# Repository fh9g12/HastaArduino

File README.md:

# HastaArduino

Bench- and wind-tunnel instrumentation for a free-to-pitch / control-surface aircraft model: firmware for a Pimoroni Pico Plus 2 (WiFi via an RM2 breakout) and the MATLAB package (`wt.hasta`) that drives it over SCPI/TCP.

**Documentation: [docs/README.md](docs/README.md)** covers the architecture, wire protocol, MATLAB package, coding conventions, testing approach, safety rules for anyone (human or agent) changing or running it, and the known gotchas and open items.

Quick orientation:

* `HastaDAQ/` is the flagship firmware; `HastaDrivers/` the shared driver library.
* `matlab/hastadaq/` is the MATLAB side (`+wt/+hasta`, `+wt/+runNum`, `+scripts`).
* `kicad/` and `wiring/` hold the schematic and cable diagrams.

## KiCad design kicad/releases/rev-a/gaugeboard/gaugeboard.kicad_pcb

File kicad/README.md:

# kicad/: schematics, PCB layout and fabrication

Everything electrical for the HastaDAQ REV A hardware. Two boards: the **main board** (`hastadaq/`) and the
**strain-gauge board** (`gaugeboard/`), joined by a 4-wire I2C loom (GND, +5V, SDA, SCL). Design decisions and
the per-board briefs are in `../docs/` (`PCB_BRIEF.md`, `PCB_BRIEF_GAUGE.md`, `PARTS_TO_SELECT.md`); the repo-wide
overview is `../docs/README.md`. This file covers the *workflow*, the *tools* and what a new agent or person
needs to know before laying out the next board.

## Status (2026-10-27)

| Board | Schematic | PCB layout | Fabrication |
|---|---|---|---|
| Gauge board (`gaugeboard/`) | done, ERC clean | **done**, DRC clean (only cosmetic library-mismatch warnings) | **ordered from PCBWay 2026-10-27** (board type, single or panel, chosen by the owner) |
| Main board (`hastadaq/`) | done, ERC clean; **changed 2026-10-27**: ENC4 removed, two RM08 SSI headers added | **done**: placed, routed, DRC clean (`releases/rev-a/hastadaq/hastadaq.kicad_pcb`) | **ordered from PCBWay 2026-10-28** |

**Both boards are in ONE final revision folder, `releases/rev-a/`** (merged 2026-10-28 from the earlier `20261026-2252-rev-a` and
`rev-a` releases, which are gone from the tree; git history has them):

* `releases/rev-a/gaugeboard/`: the gauge board as ordered (2026-10-27), with `gaugeboard.kicad_pcb` and the exact fab files in `fab/`
  (`gaugeboard_gerbers.zip` and `gerbers/`). Its `fp-lib-table` reads the shared footprints from `../hastadaq/HastaDAQ.pretty`.
* `releases/rev-a/hastadaq/`: the main board as ordered (2026-10-28; the schematic has the three SPI encoder ports ENC1-ENC3 and the
  two RM08 SSI headers J6/J11, see `../docs/PCB_BRIEF.md`), with `hastadaq.kicad_pcb` and its fab files in `fab/`.
* `releases/rev-a/docs/`, `wiring/`, `START_HERE.md`, `PUBLISHED.md`: the briefs and loom diagram from the later snapshot.
  `UoBLogo.kicad_mod` is the logo footprint from the gauge-board release.

**Commit this folder**: it is the as-built record. The gauge board's schematic was identical in both snapshots (only the netlist
timestamp differed), so nothing in the ordered gauge board changed in the merge. For a respin, `publish.py` into a NEW folder.

Not verified on hardware yet: the second ADS122C04's address (expected 0x41), I2C over the loom, servo noise
on the gauge board's 3V3. The Gerbers were checked by DRC and by counting holes against the board, not in a
third-party Gerber viewer (the owner looked at PCBWay's preview).

## Folder map

```
hastadaq/                 main board: schematic, symbol library, HastaDAQ.pretty (footprints shared by BOTH boards)
gaugeboard/               gauge board: schematic (working copy; the PCB is in a release folder, see below)
releases/<stamp>-rev-a/   frozen snapshot made by publish.py: schematics, netlists, docs and (once started) the .kicad_pcb
                          files and fab/ output. LAY OUT AND ORDER FROM A RELEASE FOLDER, never from hastadaq/ or gaugeboard/.
tools/                    generators and helpers (see below)
tools/layout/             layout, routing, silkscreen and fab scripts (see tools/layout/README.md)
```

## Workflow

1. **Schematic** (bootstrap only): `py kicad/tools/generate_gauge_sch.py` / `generate_hastadaq_sch.py`. These reassign
   reference designators and UUIDs on every run, so they are only for the time **before** a `.kicad_pcb` exists.
2. **Publish**: `py kicad/tools/publish.py --label rev-a` copies both schematics, libraries, netlists, PDFs and the docs
   into a new `releases/<date-time>-rev-a/` folder (it refuses to run if ERC is not clean). Releases are never overwritten.
3. **Lay out inside the release folder**: open `<board>.kicad_pro`, create `<board>.kicad_pcb`, Tools > Update PCB from
   Schematic. From here on **edit the schematic in KiCad and never re-run a generator over that release**. If the schematic
   needs a big change, delete or abandon the release, fix the generator, and publish a NEW one (this happened once: J3/J4
   became 2x3 headers, the first release was deleted and `20261026-2252-rev-a` replaced it; that one and `20261027-2346-rev-a-ssi` were later merged into `releases/rev-a`).
4. **Fab files**: `py kicad/tools/layout/export_fab.py releases/<rel>/<board>/<board>.kicad_pcb`
   (Gerbers + drill + zip, the PCBWay upload). Close the PCB editor first.
5. Check before ordering: `kicad-cli pcb drc --refill-zones --schematic-parity ...` shows no errors and "0 unconnected pads".

## Tools on this machine

* KiCad 10.0.6 is installed per user at `%LOCALAPPDATA%\Programs\KiCad\10.0\bin\` (not on PATH): `kicad-cli.exe` (ERC, DRC,
  netlist, Gerbers, SVG/3D render) and `python.exe` with the `pcbnew` API. Use that `python.exe` for any script that
  touches a board (the system `py` has no pcbnew).
* **No autorouter ships with KiCad.** The gauge board was routed by script (`tools/layout/gauge_route_as_built.py`).
  See "Faster routing for future boards" below.
* Previews: `kicad-cli pcb render` crops oddly; for a whole-board picture use `kicad-cli pcb export svg` (layers
  `F.Cu,B.Cu,F.SilkS,Edge.Cuts`, `--mode-single --page-size-mode 2`) and rasterise with `pymupdf`.
* `kicad-cli pcb drc --refill-zones` refills zones first; without it the report can use stale pour fills.

## Rules of the road (learned on the gauge board)

* **Check for the PCB editor before writing a board file.** A `~<name>.kicad_pcb.lck` next to the file means it is open.
  Also compare a hash of the file with your last write: the owner edits the layout by hand between your steps (they moved
  parts, resized the board, added a logo). Back the file up first. Never silently overwrite their placement.
* The owner wants **placement reviewed first, routing only after an explicit go**.
* They notice cosmetic problems: messy or ambiguous silkscreen labels, and "unnecessary" vias (stitching vias under a
  module). Look at a render of both sides before calling a layout done.
* pcbnew API notes: `pads = fp.Pads()` then iterate it (do not wrap it in `list()`); `fp.Remove(pad)` works;
  net names from the netlist start with `/` (`/+3V3`, `/SDA`); a footprint's `path` is the schematic symbol UUID, which is
  what keeps "Update PCB from Schematic" from duplicating parts. Do not name a script `inspect.py` (it shadows the stdlib).
* The ADS122C04 library footprint still carries four 2.5 mm mounting holes. On the gauge board they were removed from the
  BOARD only (`tools/layout/remove_pads.py`); "Update footprints from library" would restore them.
* **Check that every part got its nets** after building a board from a netlist: `python.exe tools/layout/check_pad_nets.py <pcb> <net>`.
  A symbol whose pin numbers differ from its footprint's pad numbers gets no nets (no ratsnest). This hit D1-D4 on the main board
  (symbol pins A/K vs KiCad diode footprints pads 1 = cathode / 2 = anode); the generators now number diode pins 1 (K) and 2 (A).
* On the main board the parts hidden under the Pico make KiCad report `pth_inside_courtyard`; the project ignores that rule (`tools/layout/set_pcbway_rules.py --ignore pth_inside_courtyard`). Run that script LAST: something in a longer command sequence reset it once.
* `lib_footprint_mismatch` DRC warnings ("local override") are cosmetic: text moved or fields edited on a footprint.
* `kicad-cli pcb export gerbers` writes a date into every file header, so re-exports differ byte-for-byte but not in content.

## Fabrication settings used (PCBWay, 2 layers)

1.6 mm FR4, 1 oz copper, min track/space 6/6 mil (0.1524 mm), min drill 0.3 mm, copper-to-edge 0.3 mm. Default net class:
0.25 mm track, 0.2 mm clearance, 0.6/0.3 mm via (`tools/layout/set_pcbway_rules.py` writes these into the `.kicad_pro`).
Stay inside 100 x 100 mm (PCBWay's cheapest quote tier). Everything on the top face, all connectors vertical 0.1 in
headers, M3 holes (3.2 mm) 4 mm in from each corner, copper pour kept 3.25 mm (radius) from each hole for the screw head.
Reference text 0.8 mm, horizontal. PCBWay's own help for the board-type options (single / panel by customer / panel by
PCBWay) is at pcbway.com/helpcenter/ordering_parameter_instruction/Board_type.html.

## Gauge board as built (rev A)

* 54.22 x 49.60 mm, 3 mm corner radius, M3 holes 46 x 41.5 mm apart. Layout (owner's final, hand-adjusted): loom J1/J2 as
  horizontal rows at the top left; C1, C2, U1 (LDO), C3, C4 and the test points down the left; R5/R6 (completion pair)
  vertical at the lower left; ADS122C04 breakouts U2 above U3, both rotated 180 degrees (digital row on top); R2/C5/R1
  between the modules and R4/C6/R3 below U3 (the optional filter positions); gauge headers J4 above J3 on the right (2x3
  each, rows V V / SIG SIG / GND GND). Logo and "STRAIN GAUGE BREAKOUT" text are on the back silkscreen.
* Routing (all scripted): horizontals on F.Cu, verticals on B.Cu; +3V3 is a trunk from the LDO to both ADCs and J3/J4;
  SDA/SCL run as a two-wire bus on the left; GND is a pour on both layers with 21 stitching vias outside the modules.
* **ADS_REF**: the two legs from the R5/R6 midpoint to R2.1 and R4.1 are equal (12.05 mm each).
* **SIG paths are not matched**: SIG1 4.7 mm, SIG2 37.2 mm, because J4 sits above J3 while R3 is at the bottom. Accepted by
  the owner (DC bridge signal); swapping J3/J4 or moving R3/C6 nearer J4 would fix it on a respin.
* Fab: 103 plated holes (0.3, 0.75, 0.8, 1.0 mm) and 4 non-plated M3 holes (3.2 mm).

## Next: the main board

* Brief: `../docs/PCB_BRIEF.md` (section 0 decisions, section 7 placement guidelines). Pico Plus 2 is 51 x 21 mm, the Pololu is
  6.1 mm tall, USB-C at the top, supply connector and Pololu at one end, loom and IMU headers at the Pico end.
* Main-board loom J2 must keep the order GND, +5V, SDA, SCL (same as gauge J1) and 3.3 V logic on SDA/SCL.
* Big supply paths: `+12V`, `VSERVO` (8.4 V, 5 A rail) and returns need wide traces or pours. Do not let the default 0.25 mm
  net class touch them.
* **Placed by the owner and first-attempt ROUTED (2026-10-28)** in `releases/rev-a/hastadaq/`: 62.1 x 89.4 mm, Pico top left, 5 V + 8.4 V supplies top right, encoders / I2C + supply cable / SBUS along the bottom, **12 small parts hidden under the Pico on the BOTTOM side** (see `../docs/PCB_BRIEF.md`) and a 20 mm plug-clearance strip behind the Pico (no COMPONENTS there; copper is allowed, `ROUTE_KEEP_TOP=1` restores the old no-top-copper rule). Routed with `tools/layout/route_main.py` (custom grid router, see `tools/layout/README.md`): VSERVO 2.0 mm bar on F.Cu down the J7 middle column, +12V 2.0 mm bar on B.Cu, +5V/+5V_VSYS 0.8 mm, +3V3 0.5 mm, signals 0.25 mm, GND pours on both layers. DRC (PCBWay 6/6 mil rules): no errors, no unconnected items; 18 `silk_over_copper` (part outlines clipped by mask, cosmetic), 1 `silk_overlap` (D4's "K" against R14), 2 `footprint_symbol_mismatch` (TP1/TP2 BOM flag), 2 `lib_footprint_mismatch` (both edited on this board only, library unchanged, so "Update footprints from library" would undo them: U2, the Pololu's three mounting holes removed with `remove_pads.py U2 --npth-only`; U1, the Pico footprint's Pico-W "Antenna Copper Keep Out" shortened by 3 mm with `trim_fp_keepout.py U1 3`, which is harmless for the Plus 2 but cuts into the antenna area if a Pico 2 W is ever fitted). The Pico mid-row GND pins 18 and 23 are bridged by a 0.5 mm B.Cu GND track across that freed strip. Fab files (7 Gerber layers + drills, zip for upload) are in `releases/rev-a/hastadaq/fab/` (made with `export_fab.py` after the owner's silkscreen edits; 4 NPTH holes, 298 PTH). Ordered from PCBWay 2026-10-28. Do NOT re-run `route_main.py` over a board whose routing the owner has edited. New this revision: the two SSI headers J6 and J11
  (3V3, GND, CLK, DATA) on GP17-GP19, which are on the Pico's lower right pins with the USB-C at the top, so place them there; the
  RLS RM08 encoders connect through inline LDB02 boards the owner fits near the Pico. The firmware for them is `HastaDrivers/src/Rm08Ssi.h`
  (PIO), not yet run on hardware.

## Faster routing for future boards

The gauge board (about 50 connections) took many iterations of hand-planned coordinates. The main board has far more
(Pico, six servo plugs, four SPI encoder ports, trigger and soft-stop circuits), so scripting every track by hand will not scale.
[KiCadRoutingTools](https://github.com/drandyhaas/KiCadRoutingTools) (MIT, Rust-accelerated A* router, KiCad 9/10, plugin and
CLI, plane pours, power-net widths, DRC and connectivity checkers) looks like a good fit **for the non-critical nets**.
This was judged from its README only; it has not been run here. Suggested trial: copy the main board, place parts by hand
first, route GND as a pour, let the tool route the logic nets, hand-route power and anything noise-critical, then run
`kicad-cli pcb drc --refill-zones` and review in KiCad. Install from KiCad's Plugin and Content Manager or build from source
rather than running an unvetted binary. Known limits per its README: no push-and-shove, no blind/buried vias; behaviour on a
2-layer through-hole board is not documented, so test before trusting.

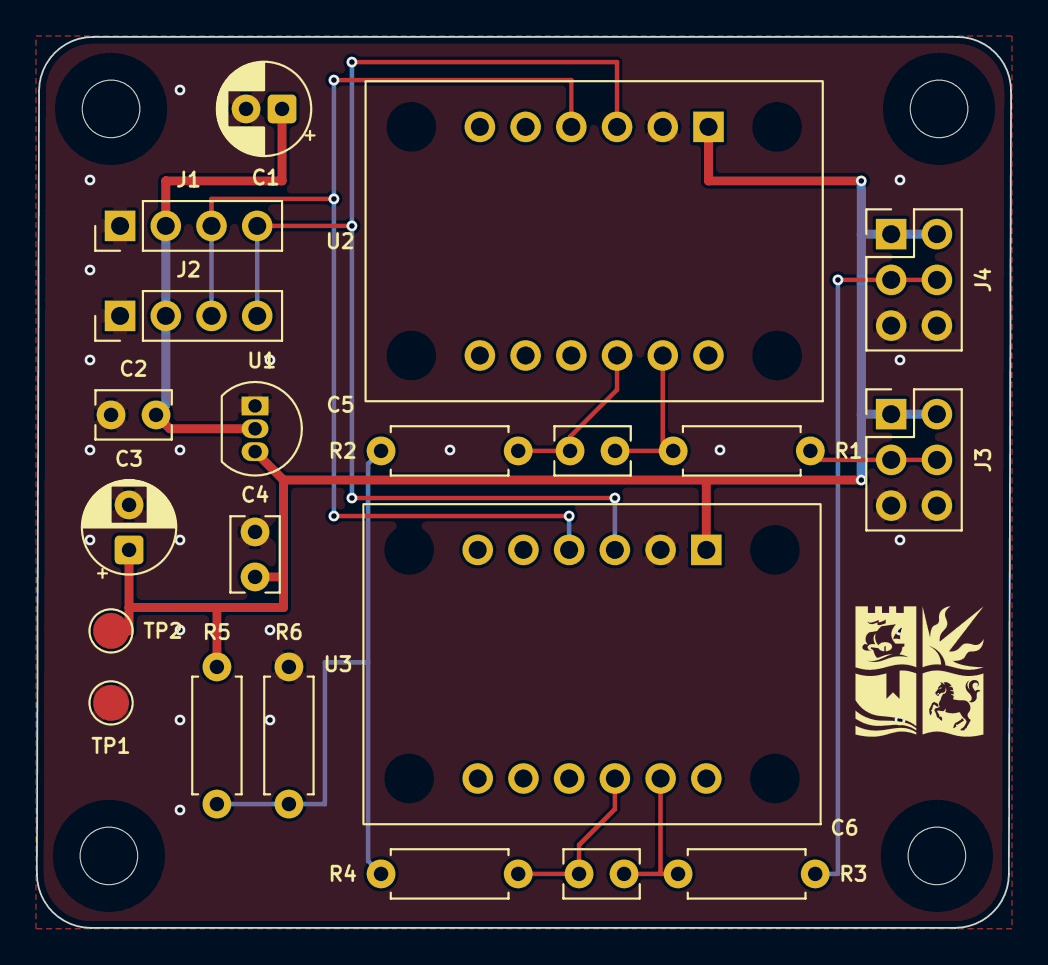
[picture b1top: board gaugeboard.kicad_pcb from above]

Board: 2 copper layers, 54.1 x 49.5 mm, 25 parts (0 on the bottom side), 12 nets.

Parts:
C1: 47uF 16V (RS PRO LHK 5x7); CP_Radial_D5.0mm_P2.00mm
C2, C4: 100nF 50V X7R (Vishay K104); C_Rect_L4.0mm_W2.5mm_P2.50mm
C3: 10uF 10V tantalum (RS PRO CB, + to 3V3); CP_Radial_D5.0mm_P2.50mm
C5, C6: 100nF 50V X7R (DNP); C_Rect_L4.0mm_W2.5mm_P2.50mm
H1, H2, H3, H4: MountingHole_3.2mm_M3
J1: LOOM from main board (4-wire I2C): GND, +5V, SDA,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; PinHeader_1x04_P2.54mm_Vertical
J2: LOOM OUT (pass-through, paralleled with J1): GND,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; PinHeader_1x04_P2.54mm_Vertical
J3: HB1 half-bridge #1 (on beam), 2x3: V V / SIG SIG 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; PinHeader_2x03_P2.54mm_Vertical
J4: HB2 half-bridge #2 (on beam), 2x3: V V / SIG SIG 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; PinHeader_2x03_P2.54mm_Vertical
R1, R2, R3, R4: 0R link; R_Axial_DIN0207_L6.3mm_D2.5mm_P7.62mm_Horizontal
R5, R6: 350R fixed; R_Axial_DIN0207_L6.3mm_D2.5mm_P7.62mm_Horizontal
TP1, TP2: TP; TestPoint_Pad_D2.0mm
U1: 3.3 V LDO: MCP1700-3302E/TO (TO-92: pin 1 GND, 2 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; TO-92_Inline
U2: Adafruit ADS122C04 #1 (I2C 0x40); Adafruit_ADS122C04_Breakout
U3: Adafruit ADS122C04 #2 (address jumper bridged); Adafruit_ADS122C04_Breakout

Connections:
/+3V3: C3.1 (+), C4.1, J3.1 (V), J3.2 (V), J4.1 (V), J4.2 (V), R5.1, TP2.1, U1.3 (VOUT), U2.1 (VIN), U3.1 (VIN)
/+5V: C1.1 (+), C2.1, J1.2 (5V), J2.2 (5V), U1.2 (VIN)
/ADS1_A0: C5.1, R1.2, U2.7 (A0)
/ADS1_A1: C5.2, R2.2, U2.8 (A1)
/ADS1_SIG: J3.3 (SIG), J3.4 (SIG), R1.1
/ADS2_A0: C6.1, R3.2, U3.7 (A0)
/ADS2_A1: C6.2, R4.2, U3.8 (A1)
/ADS2_SIG: J4.3 (SIG), J4.4 (SIG), R3.1
/ADS_REF: R2.1, R4.1, R5.2, R6.1
/GND: C1.2 (-), C2.2, C3.2 (-), C4.2, J1.1 (GND), J2.1 (GND), J3.5 (GND), J3.6 (GND), J4.5 (GND), J4.6 (GND), R6.2, TP1.1, U1.1 (GND), U2.2 (GND), U3.2 (GND)
/SCL: J1.4 (SCL), J2.4 (SCL), U2.4 (SCL), U3.4 (SCL)
/SDA: J1.3 (SDA), J2.3 (SDA), U2.3 (SDA), U3.3 (SDA)

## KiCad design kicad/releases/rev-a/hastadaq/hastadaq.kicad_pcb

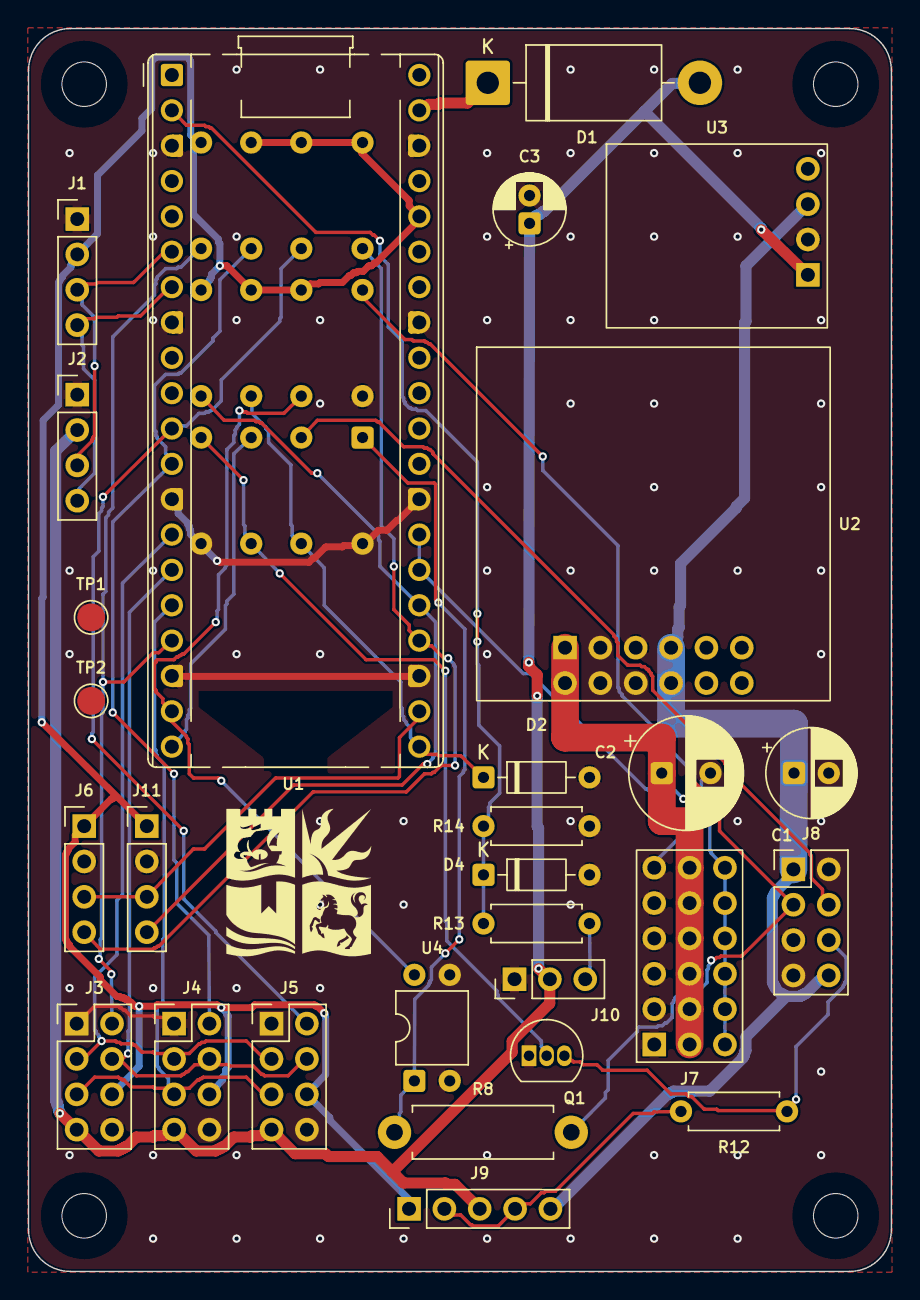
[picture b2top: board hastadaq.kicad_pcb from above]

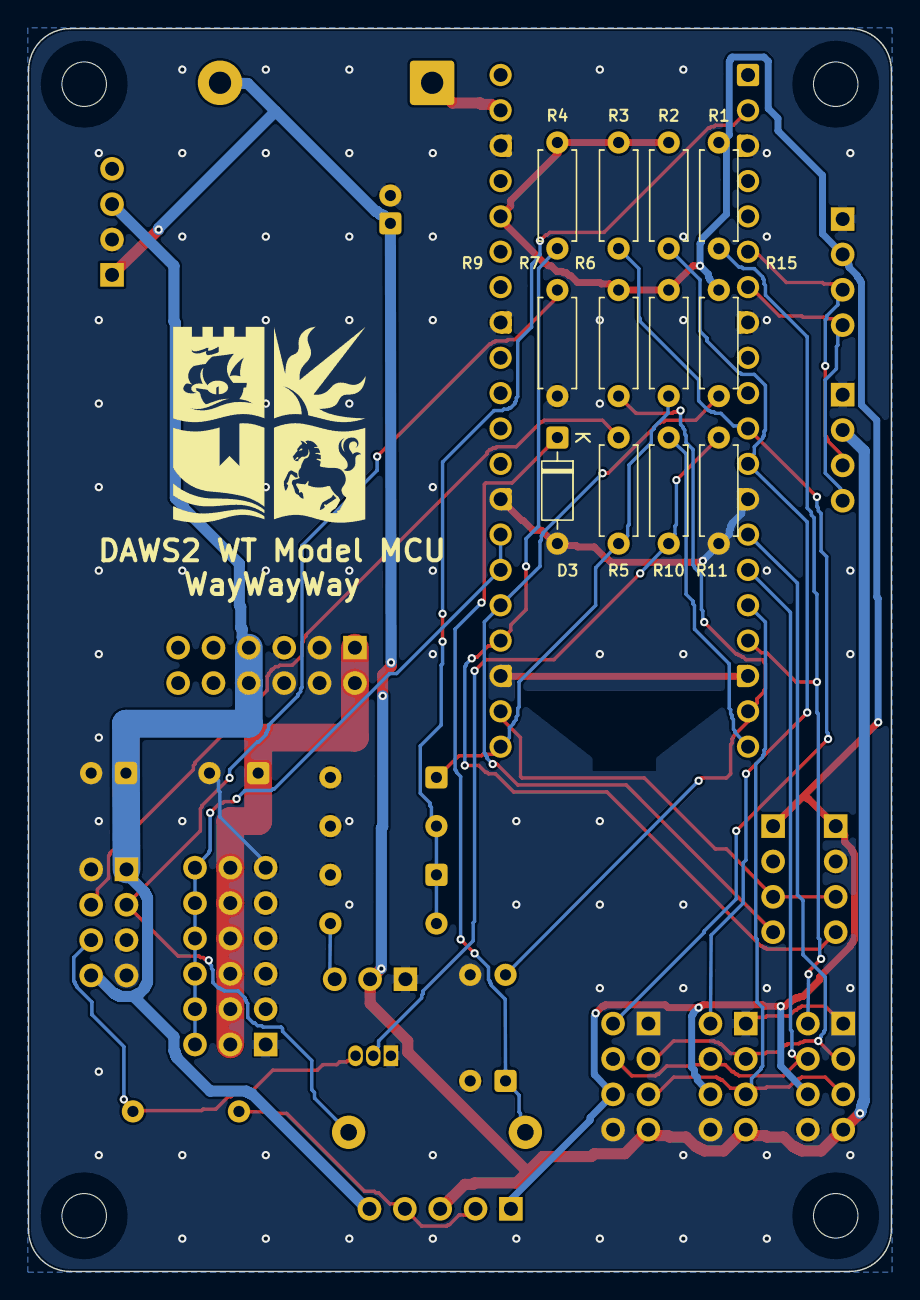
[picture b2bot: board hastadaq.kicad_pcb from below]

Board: 2 copper layers, 62.0 x 89.3 mm, 44 parts (12 on the bottom side), 29 nets.

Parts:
C1: 100uF 25V input bulk (Panasonic ECA1EM101); CP_Radial_D6.3mm_P2.50mm
C2: 470uF 16V servo bulk (Panasonic EEUFR1C471); CP_Radial_D8.0mm_P3.50mm
C3: 100uF 10V 5V bulk (RS PRO LHK 5x7); CP_Radial_D5.0mm_P2.00mm
D1: Schottky (e.g. 1N5822, 3A); D_DO-201AD_P15.24mm_Horizontal
D2: 5.1V zener (BZX55C5V1) soft-stop clamp; D_DO-35_SOD27_P7.62mm_Horizontal
D3: 1N4148 (LED reverse protect); D_DO-35_SOD27_P7.62mm_Horizontal
D4: 5.1V zener (BZX55C5V1) SBUS IN clamp; D_DO-35_SOD27_P7.62mm_Horizontal
H1, H2, H3, H4: MountingHole_3.2mm_M3
J1: IMU via Qwiic breakout (The Pi Hut 106676); PinHeader_1x04_P2.54mm_Vertical
J2: GAUGE BOARD LOOM (J_I2C): GND, +5V, SDA, SCL; PinHeader_1x04_P2.54mm_Vertical
J3: ENC1 SPI port: MT6835 (pitch); PinHeader_2x04_P2.54mm_Vertical
J4: ENC2 SPI port: MT6835; PinHeader_2x04_P2.54mm_Vertical
J5: ENC3 SPI port: RLS Orbis (or MT6835); PinHeader_2x04_P2.54mm_Vertical
J6: SSI1: RM08 encoder (3V3, GND, CLK, DATA); PinHeader_1x04_P2.54mm_Vertical
J7: SBUS servo header 3x6 (6 plugs: GND, V, SIG); PinHeader_3x06_P2.54mm_Vertical
J8: Main supply cable (2x4): VSUPPLY, VGND, TRIG, SOF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; PinHeader_2x04_P2.54mm_Vertical
J9: TRIG_OUT pull-up (1x5); PinHeader_1x05_P2.54mm_Vertical
J10: SBUS IN (RC receiver): GND, V, SIG; PinHeader_1x03_P2.54mm_Vertical
J11: SSI2: RM08 encoder (3V3, GND, CLK, DATA); PinHeader_1x04_P2.54mm_Vertical
Q1: 2N3904 NPN (TO-92, pin 1 E, 2 B, 3 C); TO-92_Inline
R1, R2, R3, R4, R15: 10k; R_Axial_DIN0207_L6.3mm_D2.5mm_P7.62mm_Horizontal
R5: 1k (soft-stop series); R_Axial_DIN0207_L6.3mm_D2.5mm_P7.62mm_Horizontal
R6: 10k (soft-stop pull-up); R_Axial_DIN0207_L6.3mm_D2.5mm_P7.62mm_Horizontal
R7: 10k pull-down; R_Axial_DIN0207_L6.3mm_D2.5mm_P7.62mm_Horizontal
R8: 1k 1W; R_Axial_DIN0411_L9.9mm_D3.6mm_P12.70mm_Horizontal
R9: 10k pull-up; R_Axial_DIN0207_L6.3mm_D2.5mm_P7.62mm_Horizontal
R10: 2.2k (base); R_Axial_DIN0207_L6.3mm_D2.5mm_P7.62mm_Horizontal
R11: 10k (base-emitter); R_Axial_DIN0207_L6.3mm_D2.5mm_P7.62mm_Horizontal
R12: 1.5k pull-up; R_Axial_DIN0207_L6.3mm_D2.5mm_P7.62mm_Horizontal
R13: 1k series; R_Axial_DIN0207_L6.3mm_D2.5mm_P7.62mm_Horizontal
R14: 10k pull-down (DNP at first); R_Axial_DIN0207_L6.3mm_D2.5mm_P7.62mm_Horizontal
TP1, TP2: TP; TestPoint_Pad_D2.0mm
U1: Pimoroni Pico Plus 2 (header pins); RaspberryPi_Pico_Common_THT
U2: Pololu D42V55F8 8.4V 5A buck (servo rail); Pololu_D42V55Fx
U3: SparkFun BabyBuck 5V (AP63357) (Pico VSYS, Orbis); SparkFun_BabyBuck_5V
U4: FOD817A opto (TRIG_IN); DIP-4_W7.62mm

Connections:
/+3V3: J1.2, J3.6, J4.6, J5.6, J6.1, J9.1, J11.1, R1.1, R2.1, R3.1, R4.1, R6.1, R9.1, R15.1, U1.36
/+5V: C3.1, D1.2, J2.2, J3.7, J4.7, J5.7, J9.3, J10.2, U3.1
/+5V_VSYS: D1.1, U1.39
/+12V: C1.1, J8.1, J8.8, J9.5, U2.7, U2.8, U3.3
/ENC1_CS: J3.2, R1.2, U1.17
/ENC2_CS: J4.2, R2.2, U1.12
/ENC3_CS: J5.2, R3.2, U1.11
/GND: C1.2, C2.2, C3.2, D2.2, D3.2, D4.2, J1.1, J2.1, J3.1, J3.8, J4.1, J4.8, J5.1, J5.8, J6.2, J7.1, J7.4, J7.7, J7.10, J7.13, J7.16, J8.2, J8.5, J8.7, J10.1, J11.2, Q1.1, R7.2, R11.2, R14.2, TP1.1, TP2.1, U1.3, U1.8, U1.13, U1.18, U1.23, U1.28, U1.33, U1.38, U2.3, U2.4, U2.5, U2.6, U3.2, U4.2, U4.3
/SBUS: J7.3, J7.6, J7.9, J7.12, J7.15, J7.18, U1.26, U1.27
/SBUS_IN: J10.3, R13.1
/SBUS_IN_GPIO: D4.1, R13.2, R14.1, U1.2
/SCL: J1.4, J2.4, U1.7
/SDA: J1.3, J2.3, U1.6
/SOFTSTOP_CABLE: J8.4, R5.1
/SOFTSTOP_IN: D2.1, R5.2, R6.2, U1.21
/SPI_MISO: J3.5, J4.5, J5.5, U1.16
/SPI_MOSI: J3.4, J4.4, J5.4, U1.15
/SPI_SCK: J3.3, J4.3, J5.3, U1.14
/SSI1_DATA: J6.4, R4.2, U1.24
/SSI2_DATA: J11.4, R15.2, U1.25
/SSI_CLK: J6.3, J11.3, U1.22
/TRIG_IN: J8.3, R7.1, R8.1
/TRIG_IN_GPIO: R9.2, U1.19, U4.4
/TRIG_IN_LED: D3.1, R8.2, U4.1
/TRIG_OUT: J8.6, Q1.3, R12.2
/TRIG_OUT_BASE: Q1.2, R10.2, R11.1
/TRIG_OUT_GPIO: R10.1, U1.20
/TRIG_PU: J9.2, J9.4, R12.1
/VSERVO: C2.1, J7.2, J7.5, J7.8, J7.11, J7.14, J7.17, U2.1, U2.2

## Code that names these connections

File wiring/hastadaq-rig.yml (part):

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connectors:
  PICO:
    type: Pimoroni Pico Plus 2
    pinlabels: [QWIIC, ENC_SCK, ENC_MOSI, ENC_MISO, ENC_CS, SBUS_SIG, TRIG_IN, TRIG_OUT, 3V3, GND]
    notes: |
      QWIIC carries I2C + 3V3/GND to the IMU/ADC chain. SBUS_SIG is
      GPIO20 (TX) and GPIO21 (RX) tied together externally at the SBUS
      connector (see SbusServoBank.h) -- shown here as one signal net.
      TRIG_IN=GPIO14, TRIG_OUT=GPIO15.

  IMU:
    type: Adafruit ICM20649 6-DoF IMU breakout
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
  SBUS_BUS:
    type: Shared SBUS bus (signal + servo power rail)
    pinlabels: [SIGNAL, VSERVO, GND]
    notes: |
      Represents the shared bus all 5 servos tap -- not a physical part,
      just this diagram's way of showing one signal/power/ground rail
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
